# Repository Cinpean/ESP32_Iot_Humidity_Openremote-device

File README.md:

# IoT Environmental Monitoring Device

## Overview

This project is an IoT environmental monitoring device developed using ESP32 microcontroller. It incorporates sensors such as BMP280, BME280, a capacitive moisture sensor, and a temperature sensor. The device is designed to collect data from its deployment area, which could be a field or any outdoor environment. It operates on a rechargeable Li-ion battery and communicates data to an OpenRemote host via the internet. Additionally, there are variants of the device, one powered by a battery and another connected to the grid, which functions as a relay controlled by an ESP8266.

## Features

- Monitoring environmental parameters including temperature, pressure, humidity, and soil moisture.
- Publishes data to an OpenRemote host for remote monitoring and analysis.
- Two variants available: battery-powered and grid-tied with relay functionality.

## Installation

### Hardware Requirements
- ESP32 microcontroller
- BMP280 sensor
- BME280 sensor
- Capacitive moisture sensor
- Temperature sensor
- Li-ion battery (for battery-powered variant)
- ESP8266 (for grid-tied variant with relay)

### Software Requirements
- ESP-IDF development framework
- MQTT library
- lwIP library
- FreeRTOS
- OpenRemote host account

### Steps
1. Clone this repository to your local machine.
2. Set up the ESP-IDF environment according to the official documentation.
3. Configure MQTT parameters in `secret.h`.
4. Flash the firmware to your ESP32 device.
5. Deploy the device in the desired location.

## Usage

1. Power on the device.
2. Ensure it is connected to the internet.
3. Data will be automatically collected from sensors and published to the configured OpenRemote host.
4. Access the OpenRemote dashboard to view real-time data and analytics.

# V1_wifi-mqtt
Change MQTT_username with the one you created on the openremote platform 

Change MQTT_password with the one on the openremote platform clients tab

Change Client_ID so that differs from 2 devices connected to same asset / server

Change MQTT_Server ip to the one of the server you are connecting to mqtt://XXX.XXX.X.XXX:1883 / 8883 

HAVE ALL THE ASSET ATTRIBUTES THE SAME AS THE ONES YOU ARE SUBSCRIBING / PUBLISHING TO  THE SAME NAME, THE SAME EVERYTING 

## Acknowledgments

- Special thanks to OpenRemote and Espressif for their support and resources.

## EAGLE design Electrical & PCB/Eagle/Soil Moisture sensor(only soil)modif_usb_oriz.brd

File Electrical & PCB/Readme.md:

Electrical diagram and PCB layout were made on Eagle, and the full 3d rendering on Fusion 360

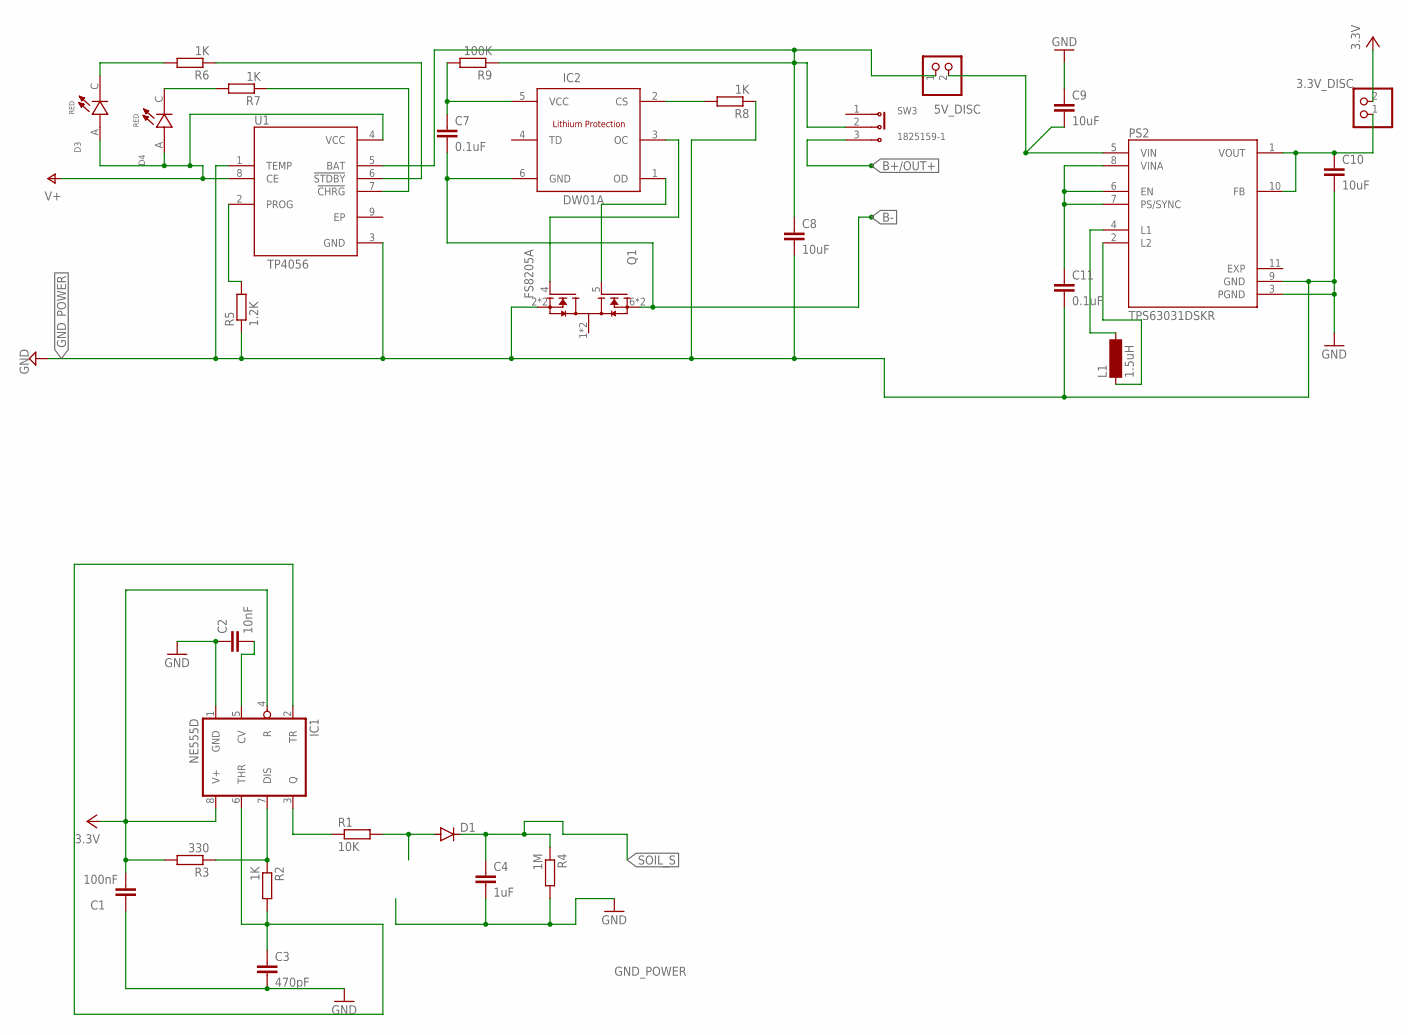
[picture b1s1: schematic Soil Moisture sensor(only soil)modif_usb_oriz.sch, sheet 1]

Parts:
3.3V_DISC, 5V_DISC: PINHD-1X2; 1X02
C1: 100nF; C0805
C2: 10nF; C0805
C3: 470pF; C0805
C4: 1uF; C0805
C7, C11: 0.1uF; C0805
C8, C9, C10: 10uF; C0805
D1: DIODE-MINIMELF; MINIMELF
D3, D4: 7012X1; LED_7012X1
IC1: NE555D; SO08
IC2: DW01A; SOT23-6
L1: 1.5uH; MS50
PS2: TPS63031DSKR; SON50P250X250X80-11N
Q1: FS8205A; SOP65P640X120-8N
R1: 10K; R0805
R2, R6, R7, R8: 1K; R0805
R3: 330; R0805
R4: 1M; R0805
R5: 1.2K; R0805
R9: 100K; R0805
SW3: 1825159-1; SW_1825159-1
U1: TP4056; SOP127P600X175-9N

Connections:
B+/OUT+: 5V_DISC.1, C8.1, R9.1, SW3.2, SW3.3, U1.5 (BAT); also elsewhere on the board
B-: C7.2, IC2.6 (GND), Q1.6 (S2), Q1.7 (S2)
GND_POWER: C1.1, C2.1, C3.2, C4.2, C8.2, C9.1, C10.2, C11.2, IC1.1 (GND), PS2.3 (PGND), PS2.9 (GND), Q1.2 (S1), Q1.3 (S1), R4.2, R5.1, R8.1, U1.1 (TEMP), U1.3 (GND); also elsewhere on the board
unnamed: IC1.7 (DIS), R2.1, R3.1
unnamed: C2.2, IC1.5 (CV)
unnamed: C3.1, IC1.2 (TR), IC1.6 (THR), R2.2
unnamed: IC1.3 (Q), R1.1
unnamed: R7.1, U1.7 (!CHRG)
unnamed: R6.1, U1.6 (!STDBY)
unnamed: R5.2, U1.2 (PROG)
unnamed: D3.C, R6.2
unnamed: D4.C, R7.2
unnamed: IC2.1 (OD), Q1.5 (G2)
unnamed: IC2.3 (OC), Q1.4 (G1)
unnamed: IC2.2 (CS), R8.2
unnamed: C7.1, IC2.5 (VCC), R9.2
unnamed: C11.1, PS2.6 (EN), PS2.7 (PS/SYNC), PS2.8 (VINA)
unnamed: L1.1, PS2.2 (L2)
unnamed: L1.2, PS2.4 (L1)
unnamed: 5V_DISC.2, C9.2, PS2.5 (VIN)
unnamed: 3.3V_DISC.1, C10.1, PS2.1 (VOUT), PS2.10 (FB)
unnamed: D1.A, R1.2
SOIL_S: C4.1, D1.C, R4.1; also elsewhere on the board
V+: D3.A, D4.A, U1.4 (VCC), U1.8 (CE); also elsewhere on the board
VCC: 3.3V_DISC.2, C1.2, IC1.4 (R), IC1.8 (V+), R3.2; also elsewhere on the board

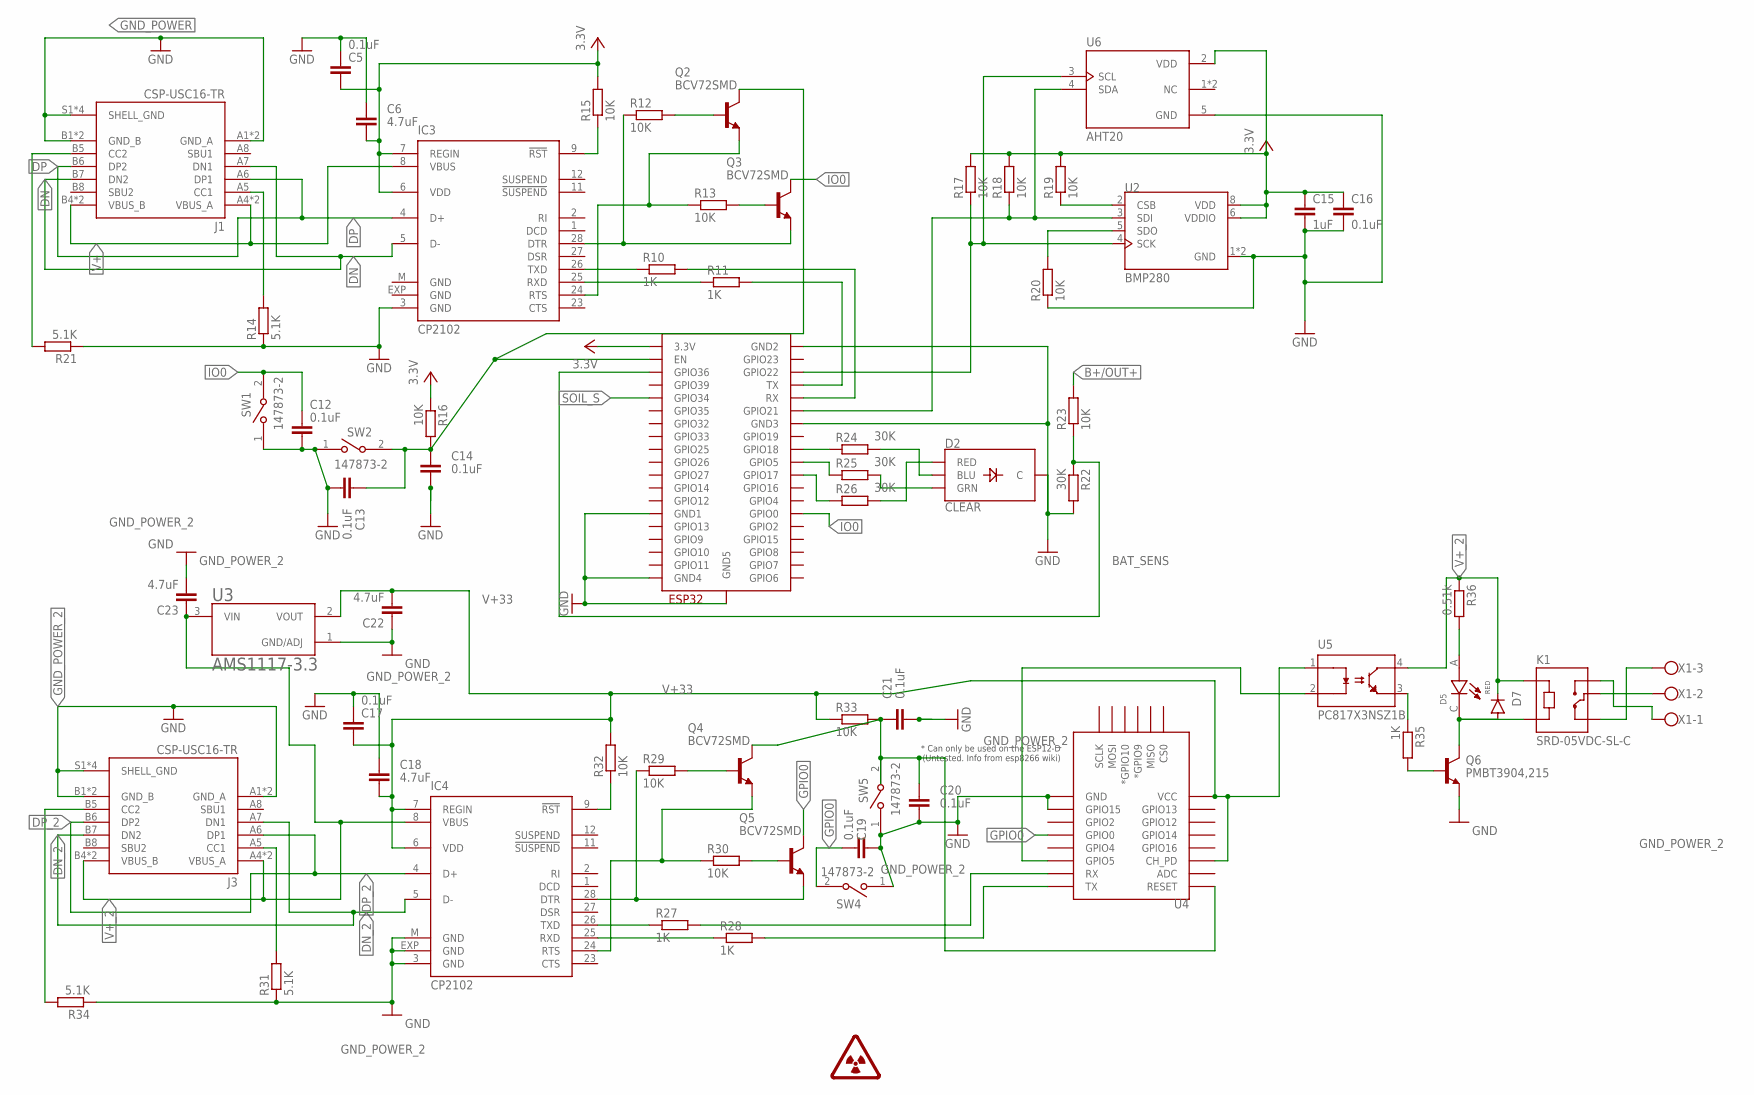
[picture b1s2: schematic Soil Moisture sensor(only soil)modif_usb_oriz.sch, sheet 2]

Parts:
C5, C12, C13, C14, C16, C17, C19, C20, C21: 0.1uF; C0805
C6, C18, C22, C23: 4.7uF; C0805
C15: 1uF; C0805
D2: CLEAR; LED-RGB-THRU
D5: 7012X1; LED_7012X1
D7: DIODE-MINIMELF; MINIMELF
IC3, IC4: CP2102; MLP28
J1, J3: CSP-USC16-TR; VALCON_CSP-USC16-TR
K1: SRD-05VDC-SL-C; RELAY_SRD-05VDC-SL-C
Q2, Q3, Q4, Q5: BCV72SMD; SOT23-BEC
Q6: PMBT3904,215; TRANS_PMBT3904,215
R10, R11, R27, R28, R35: 1K; R0805
R12, R13, R15, R16, R17, R18, R19, R20, R23, R29, R30, R32, R33: 10K; R0805
R14, R21, R31, R34: 5.1K; R0805
R22, R24, R25, R26: 30K; R0805
R36: 0.51k; R0805
SW1, SW2, SW4, SW5: 147873-2; SW_147873-2
U2: BMP280; XDCR_BMP280
U3: AMS1117-3.3; SOT229P700X180-4N
U4: ESP12ESMD; ESP12E-SMD
U5: PC817X3NSZ1B; DIP762W50P254L495H455Q4
U6: AHT20; PSON100P300X300X110-6N
U$1: ESP32-WROOM
X1: W237-103

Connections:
B+/OUT+: R23.2; also elsewhere on the board
BAT_SENS: R22.1, R23.1, U$1.SENSOR_VP (GPIO36)
DN: IC3.5 (D-), J1.A7 (DN1), J1.B7 (DN2)
DN_2: IC4.5 (D-), J3.A7 (DN1), J3.B7 (DN2)
DP: IC3.4 (D+), J1.A6 (DP1), J1.B6 (DP2)
DP_2: IC4.4 (D+), J3.A6 (DP1), J3.B6 (DP2)
GND_POWER: C5.1, C6.1, C12.2, C13.2, C14.2, C15.2, C16.2, D2.2 (C), IC3.3 (GND), IC3.EXP (GND), IC3.M (GND), J1.A1 (GND_A), J1.A12 (GND_A), J1.B1 (GND_B), J1.B12 (GND_B), J1.S1 (SHELL_GND), J1.S2 (SHELL_GND), J1.S3 (SHELL_GND), J1.S4 (SHELL_GND), R14.1, R20.1, R21.1, R22.2, SW1.1, SW2.1, U2.1 (GND), U2.7 (GND), U6.5 (GND), U$1.GND1, U$1.GND2, U$1.GND3, U$1.GND4, U$1.GND5; also elsewhere on the board
GND_POWER_2: C17.1, C18.1, C19.2, C20.2, C21.2, C22.1, C23.2, IC4.3 (GND), IC4.EXP (GND), IC4.M (GND), J3.A1 (GND_A), J3.A12 (GND_A), J3.B1 (GND_B), J3.B12 (GND_B), J3.S1 (SHELL_GND), J3.S2 (SHELL_GND), J3.S3 (SHELL_GND), J3.S4 (SHELL_GND), Q6.2 (E), R31.1, R34.1, SW4.1, SW5.1, U3.1 (GND/ADJ), U4.GND, U4.GPIO15
GPIO0: C19.1, Q5.C, SW4.2, U4.GPIO0
IO0: C12.1, Q3.C, SW1.2, U$1.IO0 (GPIO0)
unnamed: IC3.26 (TXD), R10.1
unnamed: R10.2, U$1.RX
unnamed: IC3.25 (RXD), R11.1
unnamed: R11.2, U$1.TX
unnamed: Q3.B, R13.2
unnamed: Q2.B, R12.2
unnamed: IC3.28 (DTR), Q3.E, R12.1
unnamed: IC3.24 (RTS), Q2.E, R13.1
unnamed: J1.A5 (CC1), R14.2
unnamed: C13.1, C14.1, Q2.C, R16.2, SW2.2, U$1.EN
unnamed: IC4.26 (TXD), R27.1
unnamed: R24.1, U$1.IO18 (GPIO18)
unnamed: IC3.9 (!RST), R15.1
unnamed: D2.4 (BLU), R24.2
unnamed: D2.1 (RED), R26.2
unnamed: J1.B5 (CC2), R21.2
unnamed: R19.1, U2.2 (CSB)
unnamed: R18.1, U2.3 (SDI), U6.4 (SDA), U$1.IO21 (GPIO21)
unnamed: R17.1, U2.4 (SCK), U6.3 (SCL), U$1.IO22 (GPIO22)
unnamed: R20.2, U2.5 (SDO)
unnamed: R27.2, U4.RXD0 (RX)
unnamed: IC4.25 (RXD), R28.1
unnamed: R28.2, U4.TXD0 (TX)
unnamed: Q5.B, R30.2
unnamed: R25.1, U$1.IO5 (GPIO5)
unnamed: R26.1, U$1.IO17 (GPIO17)
unnamed: D2.3 (GRN), R25.2
unnamed: Q4.B, R29.2
unnamed: IC4.28 (DTR), Q5.E, R29.1
unnamed: IC4.24 (RTS), Q4.E, R30.1
unnamed: C20.1, C21.1, Q4.C, R33.2, SW5.2, U4.RESET
unnamed: J3.A5 (CC1), R31.2
unnamed: IC4.9 (!RST), R32.1
unnamed: U4.GPIO5, U5.2 (CATHODE)
unnamed: J3.B5 (CC2), R34.2
unnamed: R35.1, U5.3 (EMITTER)
unnamed: Q6.1 (B), R35.2
unnamed: D5.C, D7.A, K1.A2, Q6.3 (C)
unnamed: K1.NC, X1.3
unnamed: D5.A, R36.2
unnamed: K1.COM, X1.2
unnamed: K1.NO, X1.1
SOIL_S: U$1.IO34 (GPIO34); also elsewhere on the board
V+: IC3.8 (VBUS), J1.A4 (VBUS_A), J1.A9 (VBUS_A), J1.B4 (VBUS_B), J1.B9 (VBUS_B); also elsewhere on the board
V+33: C17.2, C18.2, C22.2, IC4.6 (VDD), IC4.7 (REGIN), R32.2, R33.1, U3.2 (VOUT), U4.CH_PD, U4.VCC, U5.1 (ANODE)
V+_2: C23.1, D7.C, IC4.8 (VBUS), J3.A4 (VBUS_A), J3.A9 (VBUS_A), J3.B4 (VBUS_B), J3.B9 (VBUS_B), K1.A1, R36.1, U3.3 (VIN), U5.4 (COLLECTOR)
VCC: C5.2, C6.2, C15.1, C16.1, IC3.6 (VDD), IC3.7 (REGIN), R15.2, R16.1, R17.2, R18.2, R19.2, U2.6 (VDDIO), U2.8 (VDD), U6.2 (VDD), U$1.3V3 (3.3V); also elsewhere on the board

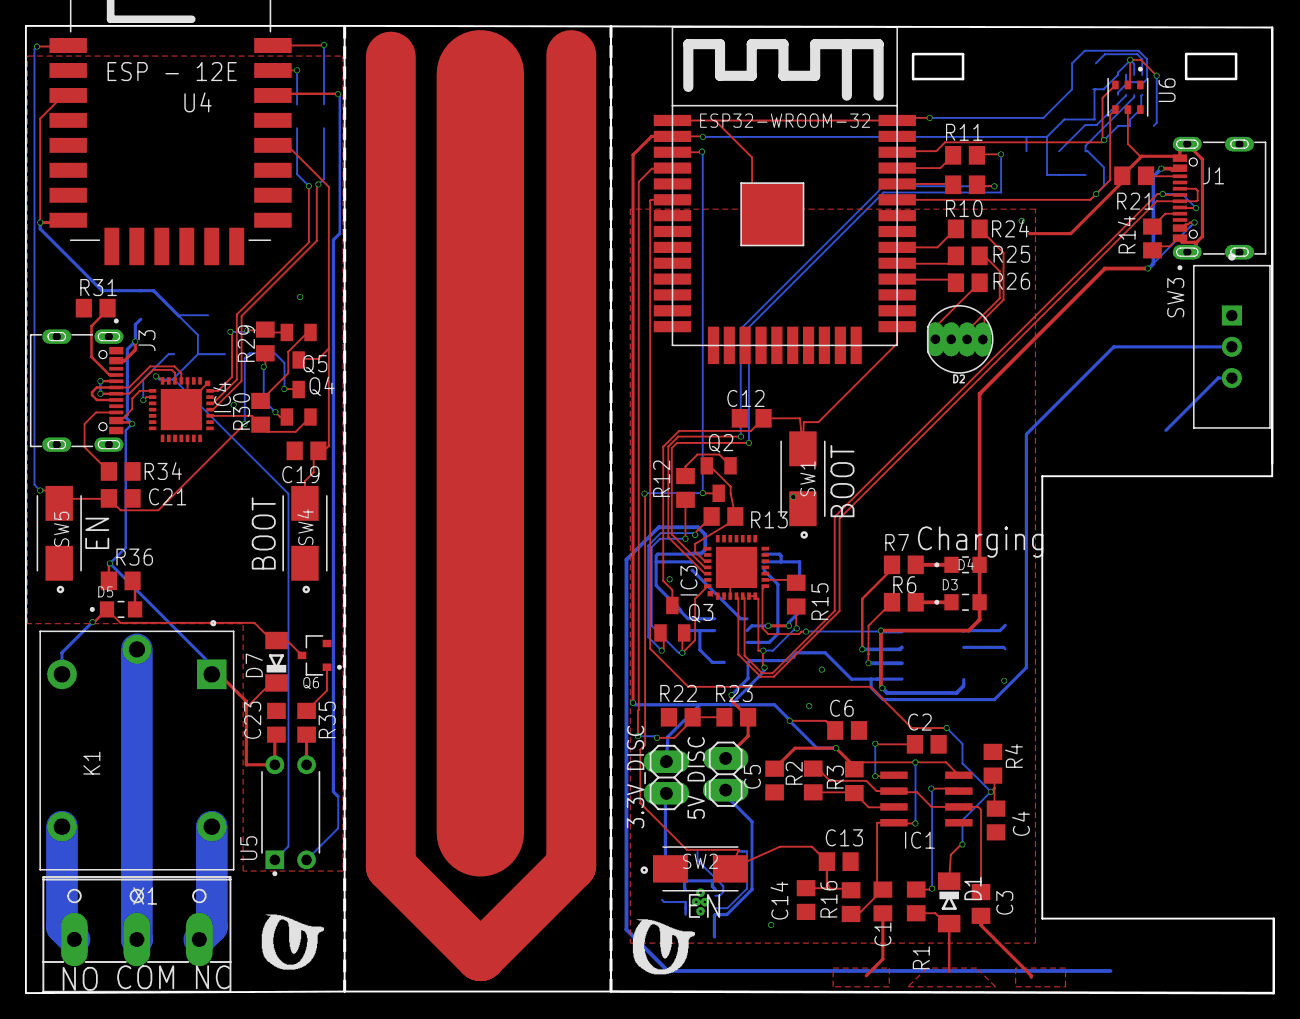
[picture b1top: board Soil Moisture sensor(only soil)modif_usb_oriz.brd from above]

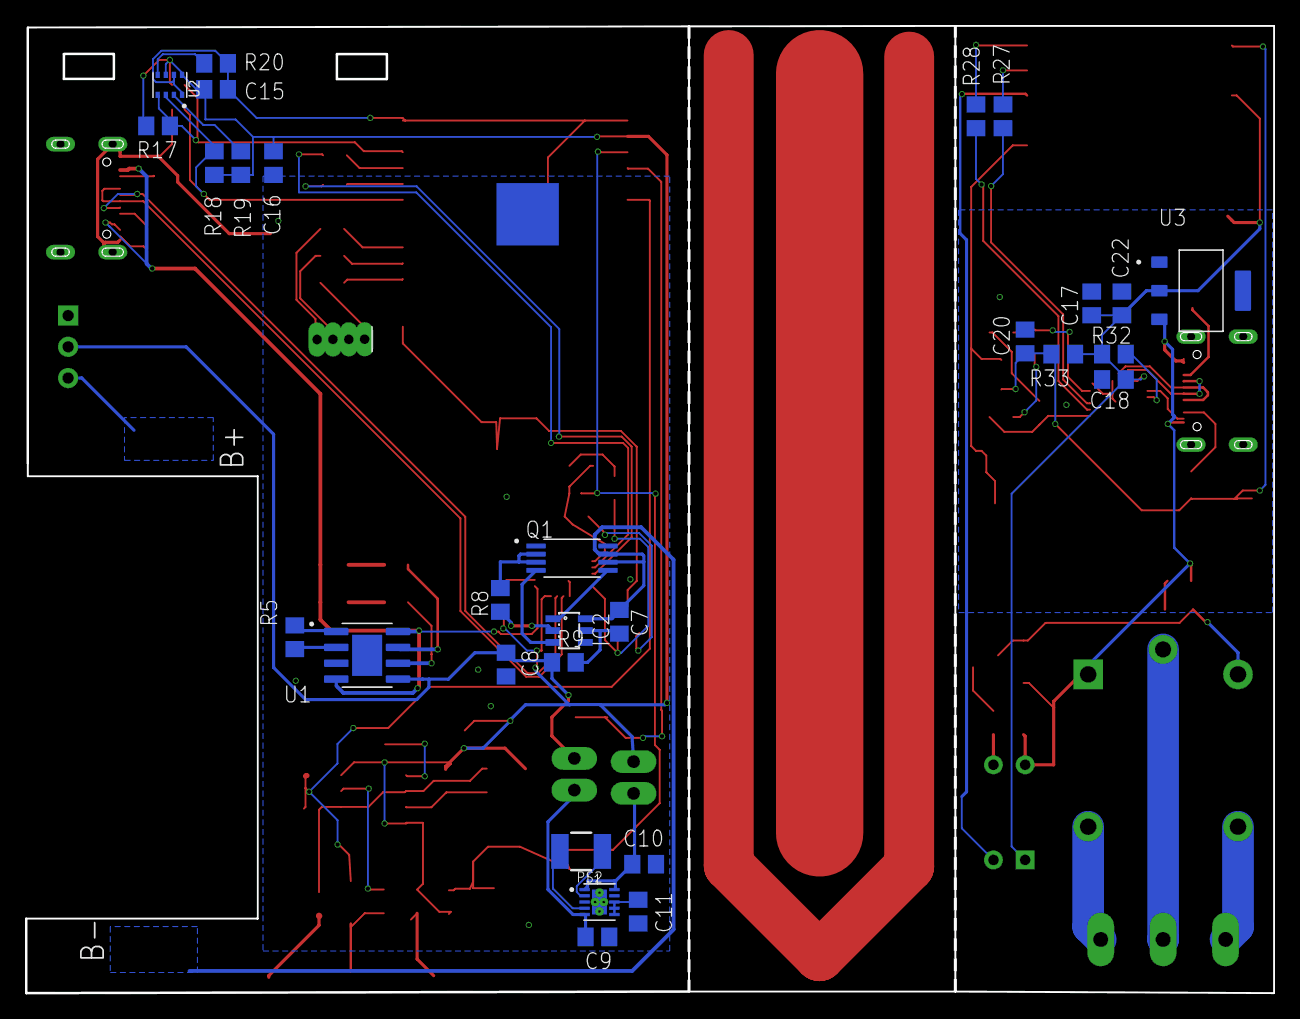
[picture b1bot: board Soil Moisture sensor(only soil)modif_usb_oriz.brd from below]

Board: 2 copper layers, 99.9 x 77.4 mm, 95 parts (29 on the bottom side), 77 nets.

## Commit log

2023-04-20 migrated from tuya
2023-04-24 added rgb led control
2023-07-05 README.md
2023-07-31 commit to be up-to-date
2023-08-02 Added flash sotrage for custom irigation date
2023-08-11 added ap capabilities and made webpage for creds
2023-08-16 added favicon
2023-09-06 refined little bit Battery sampling
2024-04-03 restructured all repo

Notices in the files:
parts and their libraries:
SparkFun-LED: Licensing: Creative Commons ShareAlike 4.0 International - https://creativecommons.org/licenses/by-sa/4.0
